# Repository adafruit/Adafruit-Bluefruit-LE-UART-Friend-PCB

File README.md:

# Adafruit Bluefruit LE UART Friend PCB
<a href="http://www.adafruit.com/products/2479"><br/>
Click here to purchase one from the Adafruit shop</a>

The Bluefruit LE UART Friend makes it easy to add Bluetooth Low Energy connectivity to anything with a hardware or software serial port. We even have nice hardware flow control so you won't have to think about losing data. Connect to your Arduino or other microcontroller or even just a standard FTDI cable for debugging and testing.

This multi-function module can do quite a lot! For most people, they'll be very happy to use the standard Nordic UART RX/TX connection profile. In this profile, the Bluefruit acts as a data pipe, that can 'transparently' transmit back and forth from your iOS or Android device. You can use our iOS App or Android App, or write your own to communicate with the UART service.

PCB files for Adafruit Bluefruit LE UART Friend. Format is EagleCAD. 
- https://www.adafruit.com/product/2479

### License

Adafruit invests time and resources providing this open source design, please support Adafruit and open-source hardware by purchasing products from [Adafruit](https://www.adafruit.com)!

All text above must be included in any redistribution

Designed by Limor Fried/Ladyada for Adafruit Industries.
Creative Commons Attribution/Share-Alike, all text above must be included in any redistribution. 
See license.txt for additional information.

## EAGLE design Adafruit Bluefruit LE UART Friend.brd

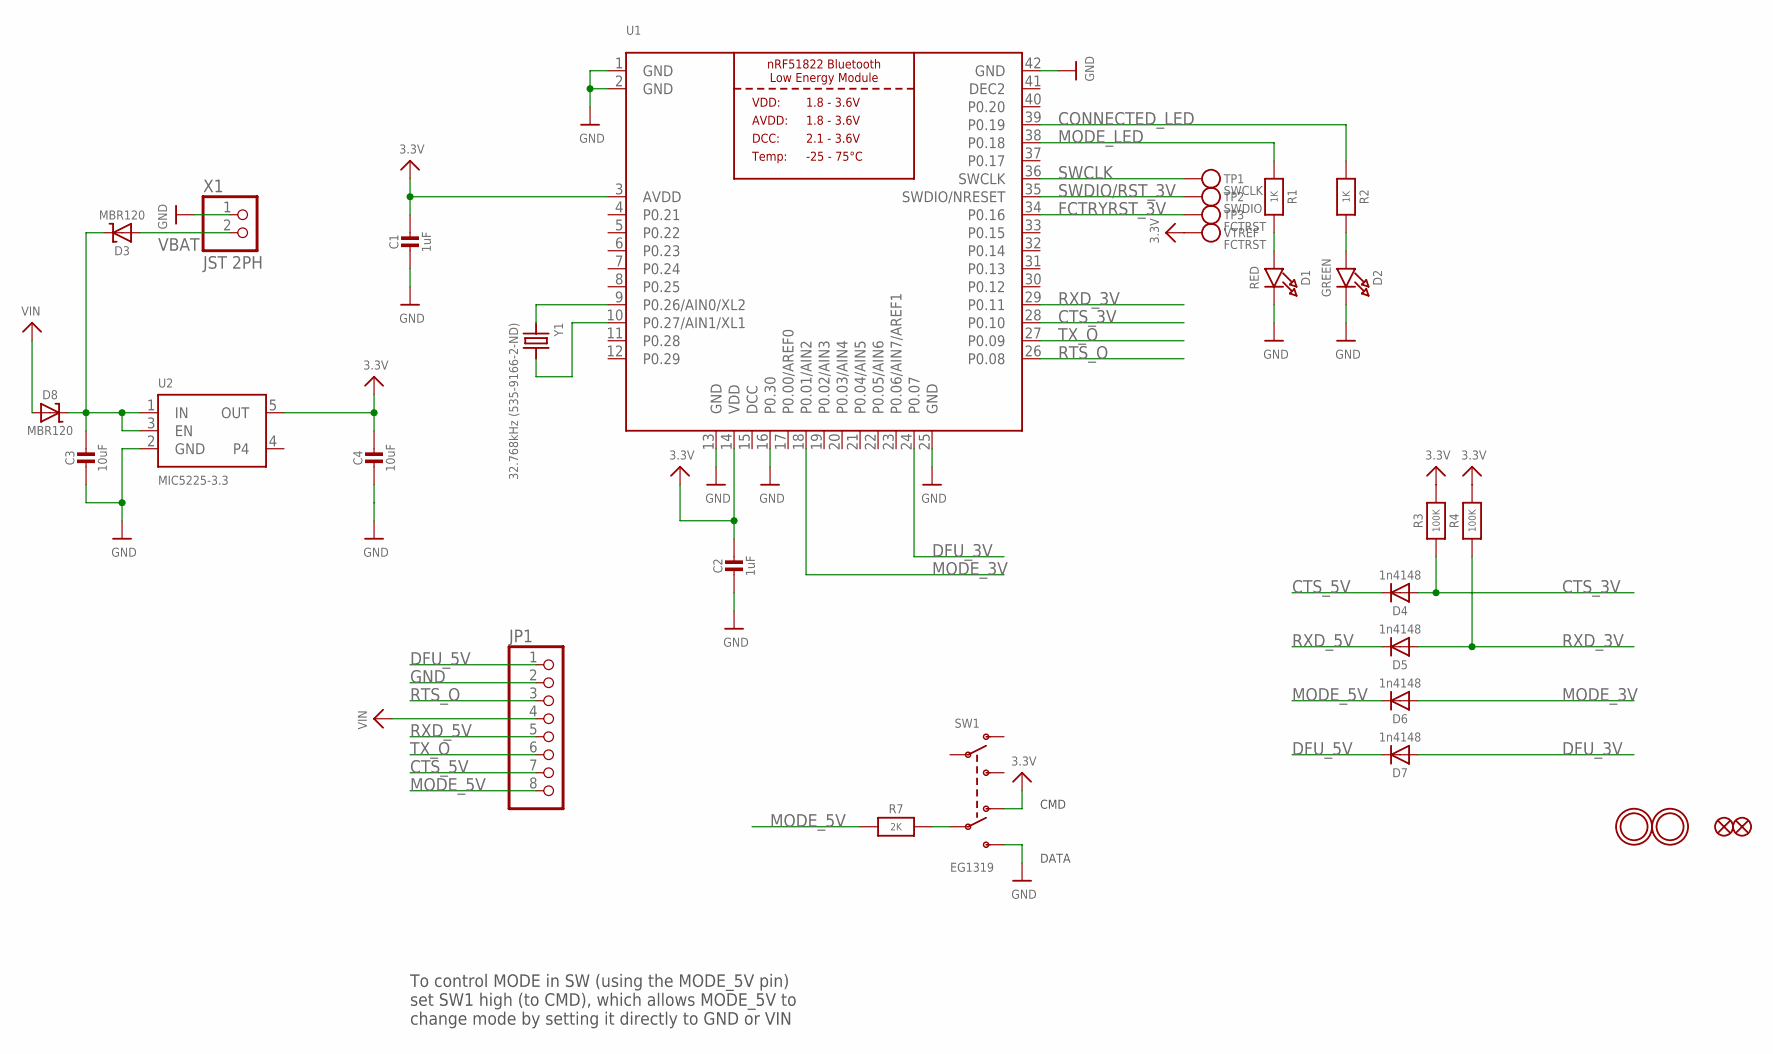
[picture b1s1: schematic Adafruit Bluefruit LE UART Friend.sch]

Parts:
C1, C2: 1uF; 0805-NO
C3, C4: 10uF; 0805-NO
D1: RED; CHIPLED_0805_NOOUTLINE
D2: GREEN; CHIPLED_0805_NOOUTLINE
D3, D8: MBR120; SOD-123
D4, D5, D6, D7: 1n4148; SOD-323
FID1, FID2: FIDUCIAL""; FIDUCIAL_1MM
JP1: HEADER-1X876MIL; 1X08_ROUND_76
R1, R2: 1K; 0805-NO
R3, R4: 100K; 0805-NO
R7: 2K; 0805-NO
SW1: EG1319; EG1390
TP1: SWCLK; PAD-1.5X2.0
TP2: SWDIO; PAD-1.5X2.0
TP3: FCTRST; PAD-1.5X2.0
U1: NRF51822_MODULE_MDBT40; BLE_MODULE_RAYTAC_MDBT40
U2: MIC5225-3.3; SOT23-5
U$28, U$29: MOUNTINGHOLE2.5; MOUNTINGHOLE_2.5_PLATED
VTREF: FCTRST; PAD-1.5X2.0
X1: JST 2PH; JSTPH2
Y1: 32.768kHz (535-9166-2-ND); CRYSTAL_CYL_2X6MM_SMT

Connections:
3.3V: C1.1, C2.1, C4.1, R3.2, R4.2, SW1.O2, U1.3 (AVDD), U1.14 (VDD), U2.5 (OUT), VTREF.P$1
CONNECTED_LED: R2.1, U1.39 (P0.19)
CTS_3V: D4.A, R3.1, U1.28 (P0.10)
CTS_5V: D4.C, JP1.7
DCC: U1.15 (DCC)
DEC2: U1.41 (DEC2)
DFU_3V: D7.A, U1.24 (P0.07)
DFU_5V: D7.C, JP1.1
FCTRYRST_3V: TP3.P$1, U1.34 (P0.16)
GND: C1.2, C2.2, C3.2, C4.2, D1.C, D2.C, JP1.2, SW1.S2, U1.1 (GND), U1.2 (GND), U1.13 (GND), U1.16 (P0.30), U1.25 (GND), U1.42 (GND), U2.2 (GND), X1.1
MODE_3V: D6.A, U1.18 (P0.01/AIN2)
MODE_5V: D6.C, JP1.8, R7.1
MODE_LED: R1.1, U1.38 (P0.18)
unnamed: U1.9 (P0.26/AIN0/XL2), Y1.1
unnamed: U1.10 (P0.27/AIN1/XL1), Y1.2
unnamed: C3.1, D3.C, D8.C, U2.1 (IN), U2.3 (EN)
unnamed: R7.2, SW1.P2
unnamed: D1.A, R1.2
unnamed: D2.A, R2.2
RTS_O: JP1.3, U1.26 (P0.08)
RXD_3V: D5.A, R4.1, U1.29 (P0.11)
RXD_5V: D5.C, JP1.5
SWCLK: TP1.P$1, U1.36 (SWCLK)
SWDIO/RST_3V: TP2.P$1, U1.35 (SWDIO/NRESET)
TX_O: JP1.6, U1.27 (P0.09)
VBAT: D3.A, X1.2
VIN: D8.A, JP1.4

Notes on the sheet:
DATA
CMD
To control MODE in SW (using the MODE_5V pin) set SW1 high (to CMD), which allows MODE_5V to change mode by setting it directly to GND or VIN

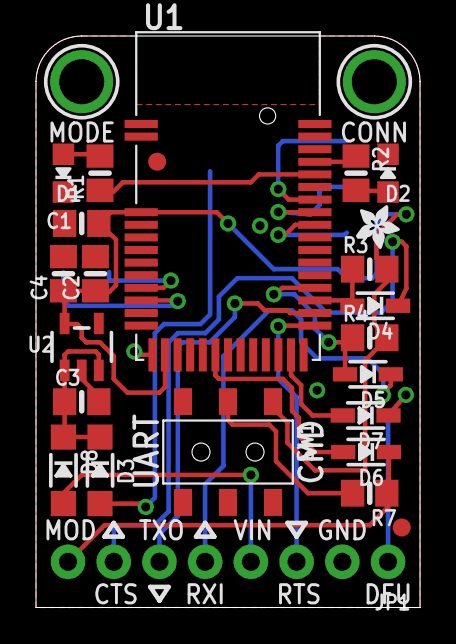
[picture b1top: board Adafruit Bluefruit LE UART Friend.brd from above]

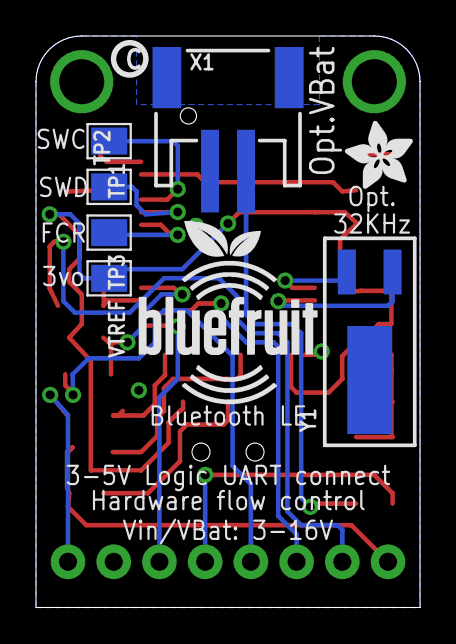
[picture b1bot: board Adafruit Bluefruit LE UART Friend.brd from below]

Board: 2 copper layers, 21.3 x 31.8 mm, 35 parts (9 on the bottom side), 25 nets.

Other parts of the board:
U$9: BLUEFRUITLOGO_100MM
U$24: PCBFEAT-REV-040
U$25: ADAFRUIT_3.5MM
U$26: ADAFRUIT_2.5MM

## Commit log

2015-06-16 init

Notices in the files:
parts and their libraries:
microbuilder: This work is placed in the public domain, and may be freely used for commercial and non-commercial work with the following conditions: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
